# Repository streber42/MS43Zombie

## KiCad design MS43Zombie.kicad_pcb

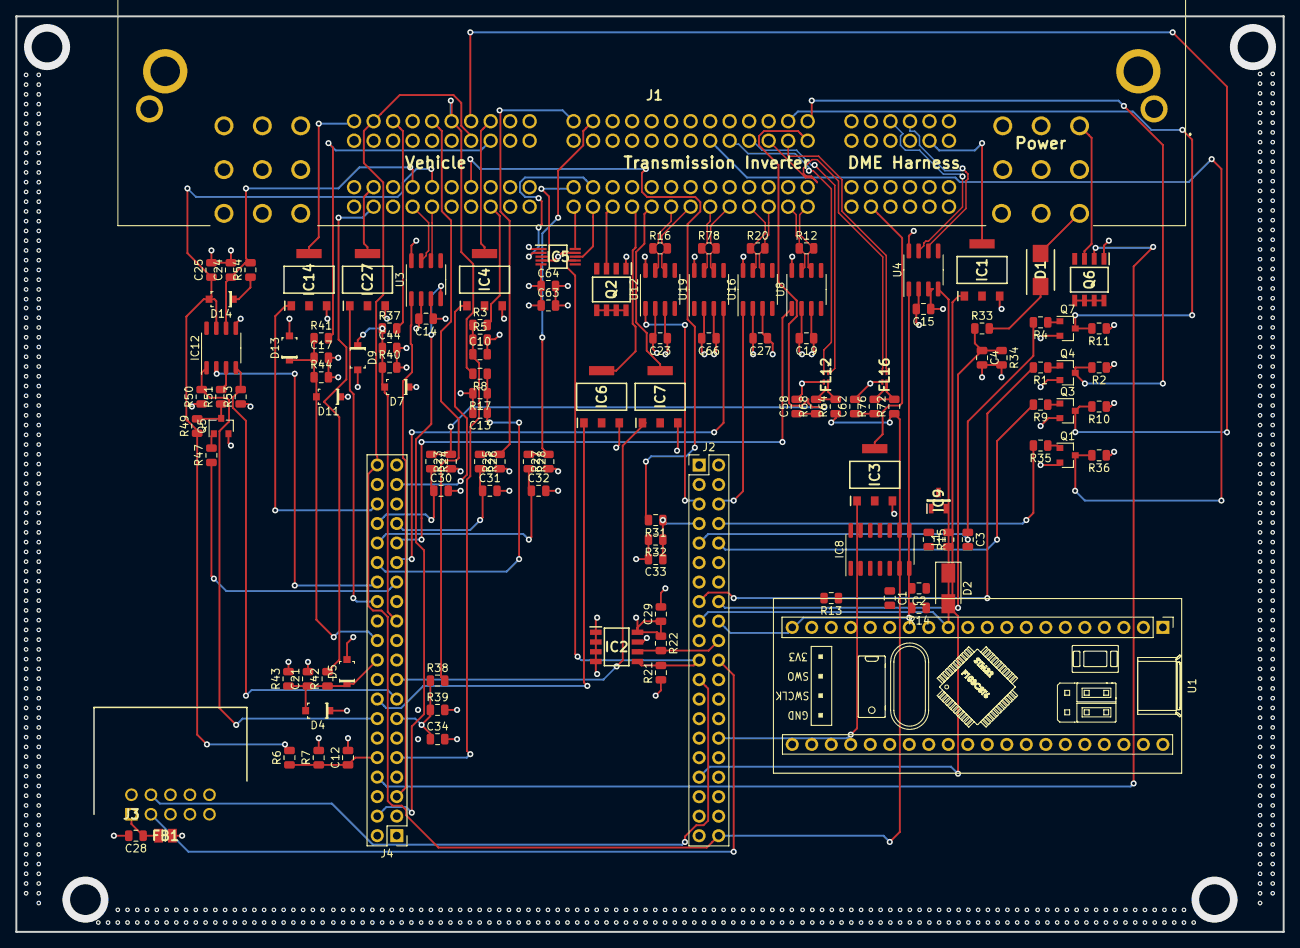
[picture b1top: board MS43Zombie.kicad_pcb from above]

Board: 4 copper layers, 165.0 x 119.2 mm, 123 parts (0 on the bottom side), 119 nets.

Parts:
C1: 100nF; C_0805_2012Metric
C2, C3: 100pF; C_0805_2012Metric
C4, C10, C12, C13, C17, C21, C25, C30, C31, C32, C33, C34, C44: 1uF; C_0805_2012Metric
C14, C15, C19, C23, C27, C58, C62, C64, C66: 0.1uF; C_0805_2012Metric
C24: 3n3; C_0805_2012Metric
C28, C63: 10uF; C_0805_2012Metric
C29: 0.1u; C_0805_2012Metric
D1: SS54B; DIOM5336X244N
D2: MRA4004T3G; D_SMA
D4, D5, D7, D9, D11, D13, D14: 1N4148W-7-F; SOD-123
FB1: MH2029-300Y; BEADC2016X130N
FL12, FL16: DLP11SA900HL2L; DLP11SA350HL2B
IC1, IC3, IC4, IC6, IC7, IC14, IC27: NCV8402ASTT1G; SOT230P700X175-4N
IC2: M24M02-DRMN6TP; SOIC127P600X175-8N
IC5: AD5243BRMZ2.5; SOP50P490X110-10N
IC8: NCV7356D1R2G; SOIC-14_3.9x8.7mm_P1.27mm
IC9: NUP1105LT1G; SOT96P237X111-3N
IC12: TJA1020T_CM,118; SO-8_3.9x4.9mm_P1.27mm
J1: 7-967288-1; 79672881
J2: EXT1; PinHeader_2x20_P2.54mm_Vertical
J3: 75867-101LF; SHDRRA10W62P254_2X5_1991X957X920P
J4: EXT2; PinHeader_2x20_P2.54mm_Vertical
L1: 47uH; L_0805_2012Metric
Q1, Q3, Q4, Q5, Q7: MMBT3904; SOT-23
Q2, Q6: NCV8461DR2G; SOIC127P600X175-8N
R1, R2, R4, R9, R10, R11, R15, R23, R24, R25, R26, R27, R28, R35, R36, R37, R40, R41, R42, R43, R44, R47, R51, R64, R68, R72, R76: 1K; R_0805_2012Metric
R3, R6, R8, R21, R22, R31, R33, R38: 4K7; R_0805_2012Metric
R5, R7, R17, R32, R34, R39: 1K5; R_0805_2012Metric
R12, R16, R20, R78: 120R; R_0805_2012Metric
R13: 2K7; R_0805_2012Metric
R14: 6K49; R_0805_2012Metric
R49: 10K; R_0805_2012Metric
R50, R53: 2K2; R_0805_2012Metric
R54: 18K; R_0805_2012Metric
U1: YAAJ_BluePill; YAAJ_BluePill_1
U3, U4, U8, U12, U16, U19: SN65HVD230; SOIC-8_3.9x4.9mm_P1.27mm

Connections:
/3_3Vcc: C14.1, C15.1, C19.1, C23.1, C27.1, C29.1, C63.1, C64.1, C66.1, D4.K, D7.K, D11.K, FB1.1, IC2.8, IC5.5, J2.1, J2.2, J4.1, J4.2, R21.1, R22.1, R23.1, R25.1, R27.1, R50.1, R53.1, U1.20, U1.38, U3.3, U4.3, U8.3, U12.3, U16.3, U19.3
/5Vcc: J1.D9, J1.D14, J2.40, J4.40, R13.2, R64.1, R72.1, U1.18
/12V_MEASURE: C4.1, J2.16, R33.1, R34.1
/12Vcc: D1.1, D2.1, R33.2
/A2076: D1.2, J1.A7
/A8680: J1.A8, R2.1, R10.1, R11.1, R36.1
/ACCompressorRelayDRV: IC27.1, J4.26
/BRAKE: C33.1, J2.7, R31.1, R32.1
/CAN1_RX: J4.4, U3.4
/CAN1_TX: J4.5, U3.1
/CAN2_RX: J2.17, U4.4
/CAN2_TX: J2.18, U4.1
/CAN+: J1.D37, U3.7
/CAN-: J1.D36, U3.6
/CAN_EXT2+: J1.B4, U4.7
/CAN_EXT2-: J1.B3, U4.6
/CLK+: J1.C47, R16.1, U12.7
/CLK-: J1.C46, R16.2, U12.6
/COOLANT_PUMP_1: J2.15, R1.2
/COOLANT_PUMP_2: J2.9, R4.2
/CoolantOutputTempSignal: J1.D39, R42.2
/CoolantTempIn: C21.1, D4.A, D5.K, J4.20, R42.1, R43.1
/DMERelayControl: IC3.4, J1.B23
/DataLinkMFW: C24.1, IC12.6, J1.D27, R54.2
/DigitalPotA1: IC5.2, J1.C38
/DigitalPotA2: IC5.8, J1.C51
/DigitalPotW1: IC5.10, J1.C52
/DigitalPotW2: IC5.3, J1.C39
/ELECTRIC_FAN: J2.10, R9.2
/EWS: J1.D33, R3.2
/FORWARD: J1.D5, R8.2
/FOR_IN: C13.1, J4.30, R8.1, R17.1
/FuelInjectorDRV: J4.8, Q6.2
/FuelInjectorRelay: J1.A1, Q6.3
/FuelPumpRelayDRV: IC14.1, J4.36
/GEAR1: C30.1, J4.34, R24.2
/GEAR2: C31.1, J4.33, R26.2
/GEAR3: C32.1, J4.32, R28.2
/HTM+: J1.C43, R20.1, U16.7
/HTM-: J1.C42, R20.2, U16.6
/IGNITION_T15: C25.1, D14.A, IC12.7, J1.D26, R6.2, R49.1
/IHKA_DEMAND_IN: J1.C3, U1.6
/INV_POWER: IC3.1, J2.30
/LIN_NSLP: IC12.2, J4.25
/LIN_WAKE: J4.27, R47.1
/MG1_TEMP+: FL12.1, J1.C17
/MG1_TEMP-: FL12.4, J1.C18
/MG1_TEMP_IN: C58.1, J4.18, R68.1
/MG2_TEMP+: FL16.1, J1.C15
/MG2_TEMP-: FL16.4, J1.C16
/MG2_TEMP_IN: C62.1, J4.19, R76.1
/MTH+: J1.C45, R78.1, U19.7
/MTH-: J1.C44, R78.2, U19.6
/OIL_POWER: IC4.1, J4.37
/OIL_PUMP_POWER: IC4.4, J1.D3
/OIL_PUMP_PWM: J1.C19, Q1.3, R36.2
/OIL_PWM: J2.8, R35.2
/PA1: J2.5, U12.1
/PA2: J2.6, U16.1
/PA3: J4.29, U19.4
/PA8: C34.1, J4.24, R38.1, R39.1
/PB8: IC2.6, IC5.6, J2.20, R22.2
/PB9: IC2.5, IC5.7, J2.21, R21.2
/PB10: J2.22, J3.3
/PB11: J2.23, J3.4
/PC0: C44.1, D7.A, D9.K, J4.23, R37.1, R40.1
/PC1: C17.1, D11.A, D13.K, J4.22, R41.1, R44.1
/PC8: IC7.1, J4.17
/PC9: IC6.1, J4.16
/PC10: IC12.4, J4.15, R53.2
/PC11: IC12.1, J4.14, R50.2
/PC12: J4.13, U1.27
/PD2: J4.6, U1.28
/PD3: J4.7, U1.7
/PD5: C10.1, J4.9, R3.1, R5.1
/PD6: C12.1, J4.10, R6.1, R7.1
/PD12: J2.32, Q2.2
/PD13: IC1.1, J2.33
/PE6: J4.31, U8.1
/PWMCoolantPump1: J1.C1, Q4.3, R2.2
/PWMCoolantPump2: J1.C2, Q7.3, R11.2
/PWMElectricFan: J1.D4, Q3.3, R10.2
/PedalSignal1: J1.D8, R37.2
/PedalSignal2: J1.D13, R41.2
/REQ+: J1.C41, R12.1, U8.7
/REQ-: J1.C40, R12.2, U8.6
/REVERSE: J1.D6, R38.2
/ReverseLightRelay: IC1.4, J1.B8
/SWCAN/CANH_EXT: C3.1, IC9.1, L1.2, R15.1
/SWCAN_MODE0: IC8.2, U1.15
/SWCAN_MODE1: IC8.3, U1.14
/SWCAN_RX: IC8.4, R13.1, U1.16
/SWCAN_TX: IC8.1, U1.17
/SignalACCompressorRelay: IC27.4, J1.D29
/SignalBrakeLightSwitch: J1.D24, R31.2
/SignalFuelPumpRelay: IC14.4, J1.D10
/TRANS_PB1: J1.C14, R23.2, R24.1
/TRANS_PB2: J1.C13, R25.2, R26.1
/TRANS_PB3: J1.C12, R27.2, R28.1
/TRANS_SL1-: IC6.4, J1.C49
/TRANS_SL2-: IC7.4, J1.C48
/TRANS_SP: J1.C50, Q2.3
GND: C1.2, C3.2, C4.2, C10.2, C12.2, C13.2, C14.2, C15.2, C17.2, C19.2, C21.2, C23.2, C24.2, C25.2, C27.2, C28.2, C29.2, C30.2, C31.2, C32.2, C33.2, C34.2, C44.2, C58.2, C62.2, C63.2, C64.2, C66.2, D5.A, D9.A, D13.A, FL12.3, FL16.3, IC1.3, IC2.1, IC2.2, IC2.3, IC2.4, IC2.7, IC3.3, IC4.3, IC5.1, IC5.4, IC5.9, IC6.3, IC7.3, IC8.8, IC9.3, IC12.5, IC14.3, IC27.3, J1.A4, J1.A5, J1.A6, J1.D7, J1.D12, J1.D38, J1.E5, J2.39, J3.2, J4.38, J4.39, Q1.2, Q2.1, Q3.2, Q4.2, Q5.2, Q6.1, Q7.2, R5.2, R7.2, R17.2, R32.2, R34.2, R39.2, R40.2, R43.2, R44.2, U1.19, U1.39, U1.40, U3.2, U3.8, U4.2, U4.8, U8.2, U8.8, U12.2, U12.8, U16.2, U16.8, U19.2, U19.8
unnamed: C1.1, C2.2, D2.2, IC8.5
unnamed: C2.1, IC8.7, L1.1, R14.1, R15.2
unnamed: C28.1, FB1.2, J3.1
unnamed: D14.K, R54.1
unnamed: FL12.2, R64.2, R68.2
unnamed: FL16.2, R72.2, R76.2
unnamed: IC8.6, R14.2
unnamed: IC12.3, R51.2
unnamed: Q1.1, R35.1
unnamed: Q2.5, Q2.6, Q2.7, Q2.8
unnamed: Q3.1, R9.1
unnamed: Q4.1, R1.1
unnamed: Q5.1, R47.2
unnamed: Q5.3, R49.2, R51.1
unnamed: Q6.5, Q6.6, Q6.7, Q6.8
unnamed: Q7.1, R4.1

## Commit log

2021-11-16 Initial checkin - copy of MS43Brakeout/Adapter
2021-11-17 Checkpoint before trying 4 layer
2021-11-18 4 layer board that passes checks
2021-11-29 Routed PCB
2022-01-19 Checkpoint 2022-01-19
    Design with bluepill to run the heater since we lose some of the SPI
    pins to the USB port on the STM32-H107.
